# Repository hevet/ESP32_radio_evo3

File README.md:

# ESP32 Web Radio Evo3 (Evolution 3)

<p align="center">

</p>

## Overview
This is project of Internet Radio Streamer called "Evo". Hardware was buid using EPS32-S3 and DAC codec PCM5102A. Construction allows to listen varius music station from all around the world.
Working properly with streams coded in MP3, AAC, VORBIS and FLAC up to 2000kbit! Support all operations like volume control, stations changes, memory bank change, power on/off on single rotary 
encoder. Support infrared remote controls working on NEC standars (38kHz) and full control over web page and Android APP.

Many people is mixing wiht others (yoRadio) - Evo is NOT based on yoRadio. Evo Radio streamer was developed entirely in Poland.

Functions:
- Internet radio stream station from bank files (can be stored on SD card/internal LittleFS or downloaded from GitHub)
- I2S simple PCM5102A decoder support
- Full web server integrated for controling from desktop computer or mobile phone
- OLED Display SSD1322, SH1122 (256px x 64px)
- Single rotary encoder operations 
- OTA updates directlly from web page
- SD card /LittleFS content review/upload/download/delete by web page
- VUmeters add as some visualization on OLED
- 16 Banks with 99 station per each Bank support
- Polish fonts add for coorrect display station strings
- 3-point Equalizer
- ADC resistance keyboard support for easy inegration in FM converted tuners
- Power on/off from remote controller
- Sleep timer

## FLAC stations
<p>Smoothjazz.com.pl 16bit 1Mbps and AIDA Radio 24bit 2Mpbs!
<br>

<p>

## Display Modes

## Hardware
- ESP32-S3 dev. module with internal antena or external antena connector
- 256x64 OLED display based on SSD1322 or SH1122 driver IC
- 1x Rotary encoder
- IR 38KHz receiver (Vishay TSOP2238)
- PCB design stored in repository
- Housing avalivle as ready to print STL files
- SD or micro SD card reader (optional)
 
## Software
Project was coded in Arduino but ready main.cpp for Platformio files avalable and also tested

How to compile (Arduino):
- Install fresh Arduino (currently 2.3.6)
- After instalation add ESP32 board package by Espressif (this operation will take some time)
- Install bellow libs inside Arduino (library manager): 
  ESP32-audioI2S, 
  ezButton, 
  U8g2, 
  WiFiManager

Proper version of all libs are placed on top of source code ino file
For Platformio look into src folder -> Platformio folder and Platformio.ini file.

## Software Dependencies
[ESP Espressif 3.3.7 libs]

[3rd-party libs]
- ESP32-audioI2S-master 3.4.4
- U8g2 2.36.5
- ezButton 1.0.4
- WiFiManager 2.0.17
- ESP Async WebServer 3.10.0
- Async TCP 3.4.10

## Web server
Radio has buit in small web server with simple webpage for list stations, bank select, volume control and access to settings menu

## Radio Browser
The built-in Radio Browser search page allows you to search for various radio stations around the world, and play or test them instantly on Evo Radio.

## Android APK
There is small Android APK wirtten for this project giving possibily to direct control Evo radio from mobile phone.

There is a pre-coded remote controller RC-406 (Kenwood clone). You can change the settings via a simple web interface or by editing the remote.txt file stored in memory (SD card or internal flash).

Key mapping:

## Usage
Minimum radio can be build only with two compoents - ESP32-S3 dev. module and PCM5102A. In this configartion last station, memory bank number and volume will be stored in EEPROM. Control is possible via web page or IR remote control RC-406.
For full experience connect encoder, IR receiver.

NEC standard codes for remote controler are stored in "remote.txt" file. You can learn your IR remote by webpage. 

### Radio Station URLs
The radio streams URL addresses are defined in banks files, each bank is downloaded at first run and stored on SD card as separate txt file: Bank01.txt, Bank02.txt etc.
Each of banks can store 99 station. You can modify the station by changing the URLs in the code. Bank files are stored here:

STATIONS_URL1 "https://raw.githubusercontent.com/dzikakuna/ESP32_radio_streams/main/bank01.txt"
STATIONS_URL2 "https://raw.githubusercontent.com/dzikakuna/ESP32_radio_streams/main/bank02.txt"
STATIONS_URL3 "https://raw.githubusercontent.com/dzikakuna/ESP32_radio_streams/main/bank03.txt"
...
STATIONS_URL16 "https://raw.githubusercontent.com/dzikakuna/ESP32_radio_streams/main/bank16.txt"

## License
This project is open-source and licensed under the [MIT License](https://opensource.org/licenses/MIT). 
Feel free to contribute and improve the code.

MIT License
Copyright (c) 2025 [Grzegorz / Dzikakuna / Robgold ]

Permission is hereby granted, free of charge, to any person obtaining a copy of this software and associated documentation files (the "Software"), to deal in the Software without restriction, including without limitation the rights to use, copy, modify, merge, publish, distribute, sublicense, and/or sell copies of the Software, and to permit persons to whom the Software is furnished to do so, subject to the following conditions:
The above copyright notice and this permission notice shall be included in all copies or substantial portions of the Software.
THE SOFTWARE IS PROVIDED "AS IS", WITHOUT WARRANTY OF ANY KIND, EXPRESS OR IMPLIED, INCLUDING BUT NOT LIMITED TO THE WARRANTIES OF MERCHANTABILITY, FITNESS FOR A PARTICULAR PURPOSE AND NONINFRINGEMENT. IN NO EVENT SHALL THE AUTHORS OR COPYRIGHT HOLDERS BE LIABLE FOR ANY CLAIM, DAMAGES OR OTHER LIABILITY, WHETHER IN AN ACTION OF CONTRACT, TORT OR OTHERWISE, ARISING FROM, OUT OF OR IN CONNECTION WITH THE SOFTWARE OR THE USE OR OTHER DEALINGS IN THE SOFTWARE.

## Others
- This project was inspired by https://github.com/sarunia/ESP32_radio_player_v2
- More informations you can read here: https://www.elektroda.pl/rtvforum/topic4041603.html

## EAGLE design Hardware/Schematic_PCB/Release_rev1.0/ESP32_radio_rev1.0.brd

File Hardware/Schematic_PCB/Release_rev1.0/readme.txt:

ESP32 Internet Radio schematic & PCB file - rev 1.0
Gerbers attached. Drills in english (2.4) and metric format (3.3)
TootTable attached from CAM system.

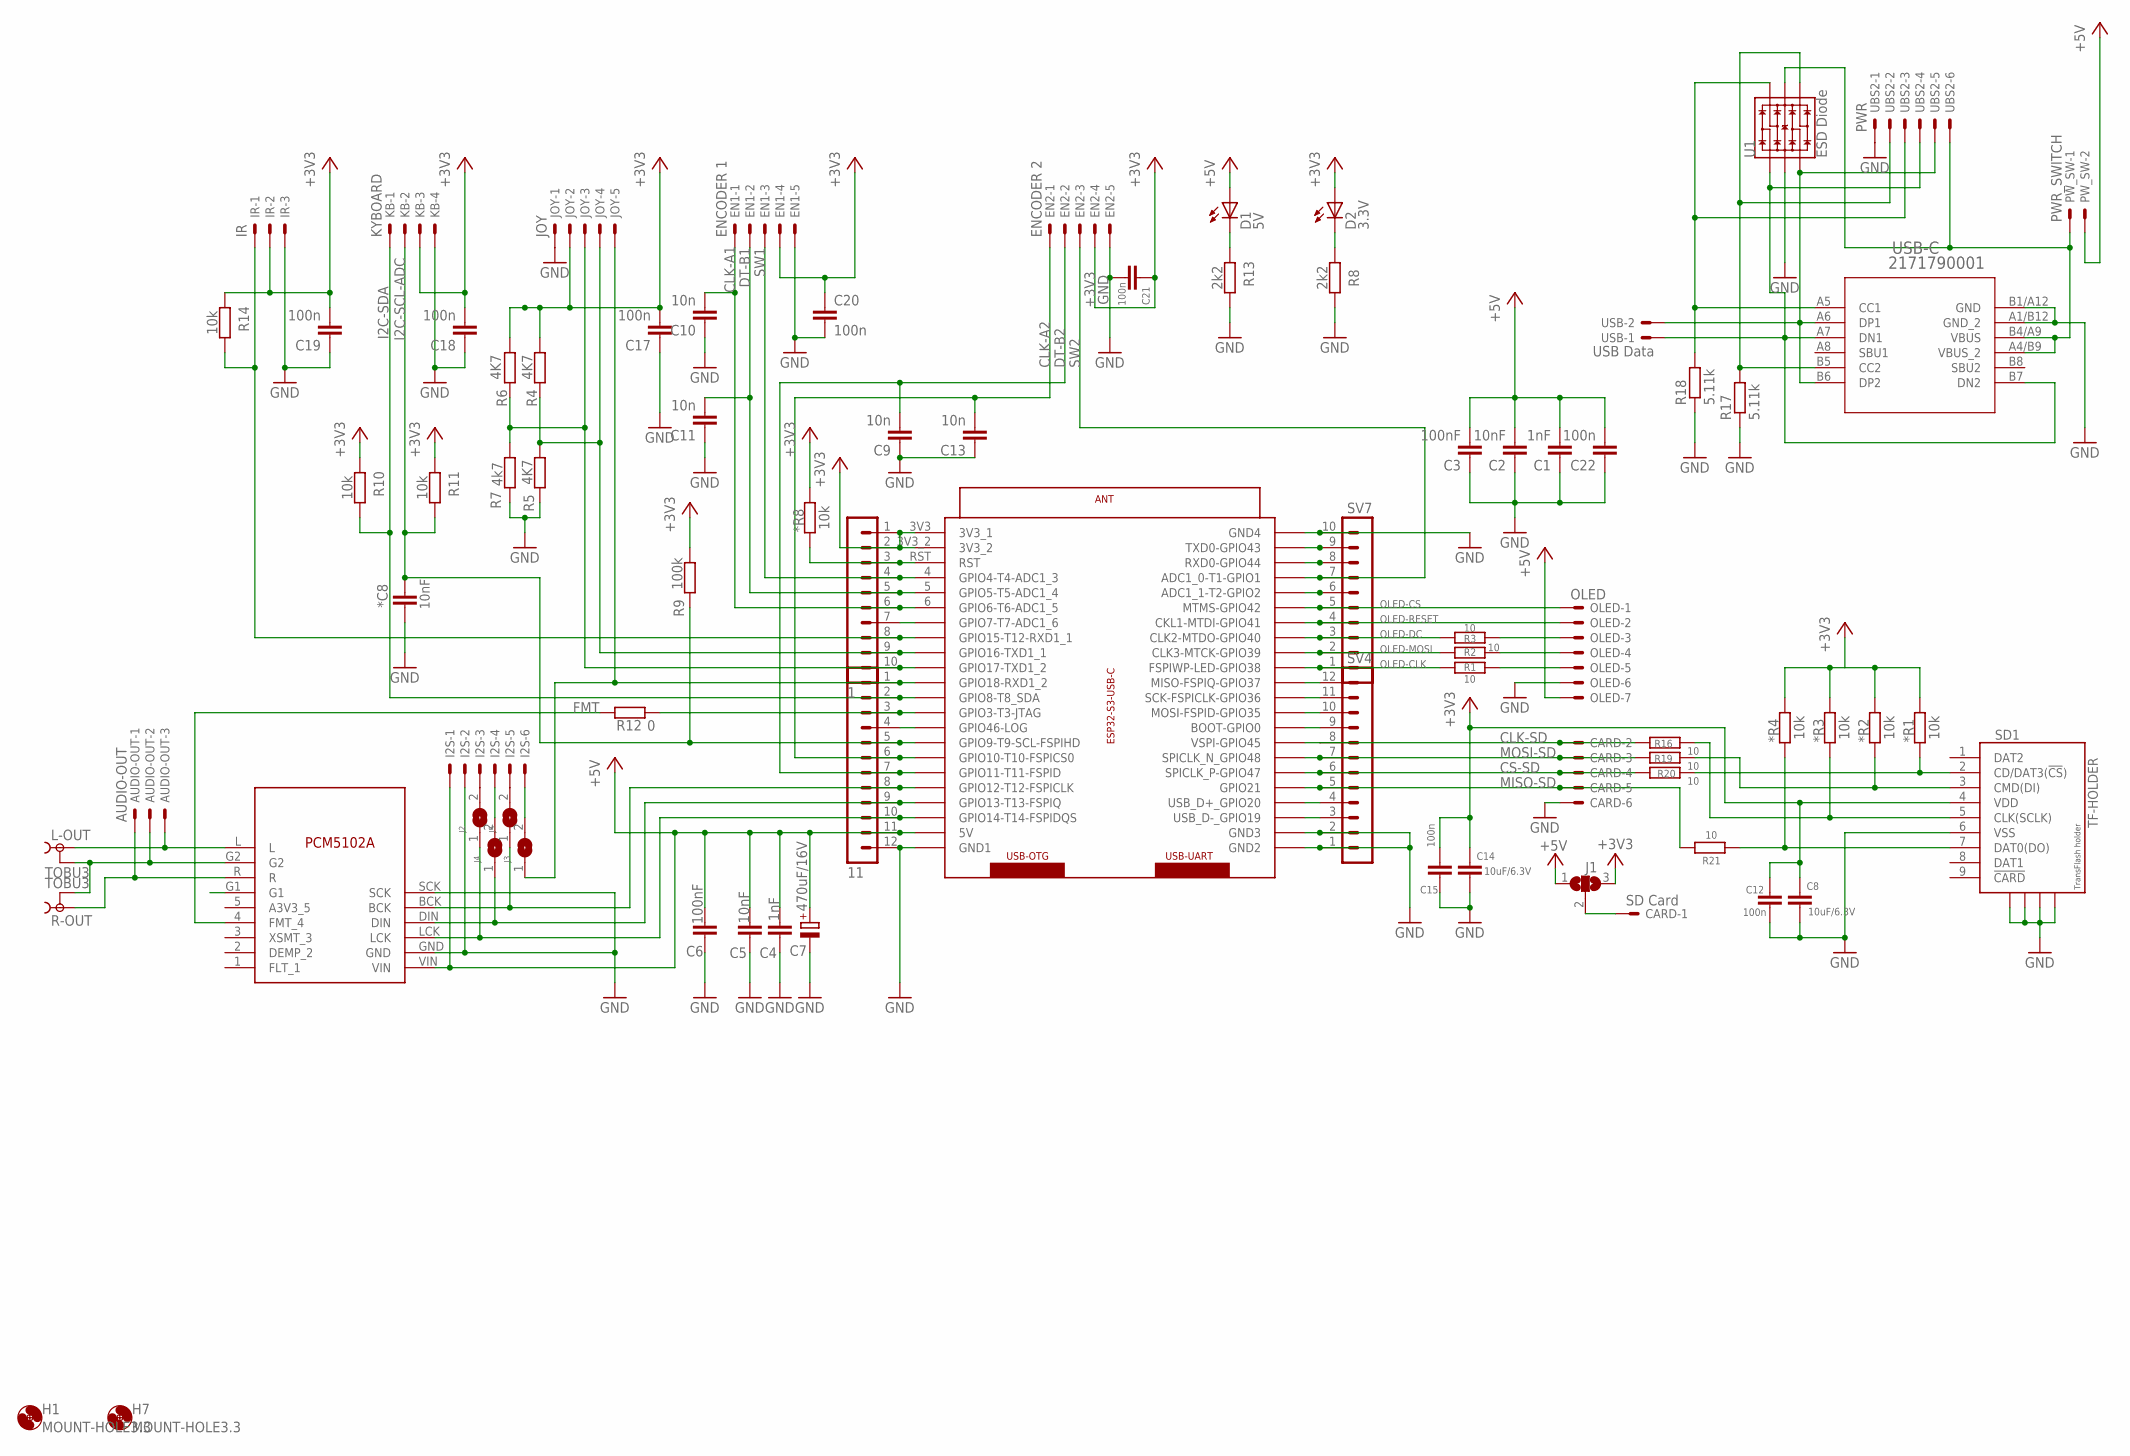
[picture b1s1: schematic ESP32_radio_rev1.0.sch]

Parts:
1: MA10-1
11: MA12-1
*C8: 10nF; C0603
*R1, *R2, *R3, *R4, *R8: 10k; R0603
AUDIO-OUT: AUDIO-OUT; JST-XH-03-PACKAGE-LONG-PAD
C1, C4: 1nF; C0603
C2, C5: 10nF; C0603
C3, C6: 100nF; C0603
C7: 470uF/16V; 150CLZ-1010
C8, C14: 10uF/6.3V; C1210
C9, C10, C11, C13: 10n; C0603
C12, C15, C17, C18, C19, C20, C21, C22: 100n; C0603
CARD: SD Card; JST-XH-06-PACKAGE-LONG-PAD
D1: 5V; CHIP-LED0805
D2: 3.3V; CHIP-LED0805
EN1: ENCODER 1; JST-XH-05-PACKAGE-LONG-PAD
EN2: ENCODER 2; JST-XH-05-PACKAGE-LONG-PAD
H1, H7: MOUNT-HOLE3.3; 3,3
I2S: JST-XH-06-PIN-LONG-PAD; JST-XH-06-PACKAGE-LONG-PAD
IR: IR; JST-XH-03-PACKAGE-LONG-PAD
J1: SJ2W; SJ_2
J2, J3, J4, J5: SJ
JOY: JOY; JST-XH-05-PACKAGE-LONG-PAD
KB: KYBOARD; JST-XH-04-PACKAGE-LONG-PAD
L-OUT: TOBU3
M2: I2S_PCM_51XX_SOUNDCARD; I2S_PCM_5100_SOUNDCARD
OLED: OLED; JST-XH-07-PACKAGE-LONG-PAD
PW_SW: PWR_SWITCH; JST-XH-02-PACKAGE-LONG-PAD
R1, R2, R3, R16, R19, R20, R21: 10; R0603
R4, R5, R6: 4K7; R0603
R7: 4k7; R0603
R8, R13: 2k2; R0603
R9: 100k; R0603
R10, R11, R14: 10k; R0603
R12: 0; R0603
R17, R18: 5.11k; R0603
R-OUT: TOBU3
SD1: TF-HOLDER; TF-PULL
SV4: MA12-1
SV7: MA10-1
U1: ESD Diode; SOT-23-6
U$1: ESP32-S3-USBC
UBS2: PWR; JST-XH-06-PACKAGE-LONG-PAD
USB: USB Data; JST-XH-02-PACKAGE-LONG-PAD
USB-C: 2171790001; 2171790001_MOL

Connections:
5V_USB: PW_SW.1, U1.5 (VCC), UBS2.6, USB-C.A4/B9 (VBUS_2), USB-C.B4/A9 (VBUS)
+3V3: 1.1, 1.2, *R1.1, *R2.1, *R3.1, *R4.1, *R8.1, C8.1, C12.2, C14.1, C15.2, C17.2, C18.2, C19.2, C20.1, C21.1, D2.A, EN1.4, EN2.4, IR.2, J1.3, JOY.2, KB.3, R4.2, R6.2, R9.2, R10.2, R11.2, R14.2, SD1.4 (VDD), U$1.3V3 (3V3_1), U$1.3V3_2
+5V: 11.11, C1.2, C2.2, C3.2, C4.2, C5.2, C6.2, C7.+, C22.2, D1.A, I2S.1, J1.1, M2.VIN, OLED.7, PW_SW.2, U$1.5V
ANALOGGND: AUDIO-OUT.2, L-OUT.2, L-OUT.2@1 (2), L-OUT.2@2 (2), M2.G2, R-OUT.2, R-OUT.2@1 (2), R-OUT.2@2 (2)
CLK-A1: 1.6, C10.2, EN1.1, U$1.6 (GPIO6-T6-ADC1_5)
CLK-A2: 11.6, C13.2, EN2.1, U$1.10 (GPIO10-T10-FSPICS0)
CLK-SD: CARD.2, R16.1, SV4.8, U$1.45 (VSPI-GPIO45)
CS-SD: CARD.4, R20.1, SV4.6, U$1.47 (SPICLK_P-GPIO47)
DN: U1.1 (IO1), UBS2.4, USB.1, USB-C.A7 (DN1), USB-C.B7 (DN2)
DP: U1.3 (IO2), UBS2.5, USB.2, USB-C.A6 (DP1), USB-C.B6 (DP2)
DT-B1: 1.5, C11.2, EN1.2, U$1.5 (GPIO5-T5-ADC1_4)
DT-B2: 11.7, C9.2, EN2.2, U$1.11 (GPIO11-T11-FSPID)
FMT: M2.4 (FMT_4), R12.2
FMT1: 11.4, U$1.46 (GPIO46-LOG)
GND: 11.12, *C8.2, C1.1, C2.1, C3.1, C4.1, C5.1, C6.1, C7.-, C8.2, C9.1, C10.1, C11.1, C12.1, C13.1, C14.2, C15.1, C17.1, C18.1, C19.1, C20.2, C21.2, C22.1, CARD.6, EN1.5, EN2.5, I2S.2, IR.3, JOY.1, KB.4, M2.GND, M2.SCK, OLED.6, R5.1, R7.1, R8.1, R13.1, R17.1, R18.1, SD1.6 (VSS), SD1.S1, SD1.S2, SD1.S3, SD1.S4, SV4.1, SV4.2, SV7.10, U1.2 (VSS), U$1.GND1, U$1.GND2, U$1.GND3, U$1.GND4, UBS2.1, USB-C.A1/B12 (GND_2), USB-C.B1/A12 (GND)
I2C-SCL-ADC: 11.5, *C8.1, KB.2, R9.1, R11.1, U$1.9 (GPIO9-T9-SCL-FSPIHD)
I2C-SDA: 11.2, KB.1, R10.1, U$1.8 (GPIO8-T8_SDA)
MISO-SD: CARD.5, R21.1, SV4.5, U$1.21 (GPIO21)
MOSI-SD: CARD.3, R19.1, SV4.7, U$1.48 (SPICLK_N_GPIO48)
unnamed: AUDIO-OUT.1, M2.R, R-OUT.1
unnamed: AUDIO-OUT.3, L-OUT.1, M2.L
unnamed: OLED.5, R1.2
unnamed: OLED.4, R2.2
unnamed: OLED.3, R3.2
unnamed: *R4.2, R21.2, SD1.7 (DAT0(DO))
unnamed: 1.10, JOY.3, R6.1, R7.2, U$1.17 (GPIO17-TXD1_2)
unnamed: 11.1, J3.1, JOY.5, U$1.18 (GPIO18-RXD1_2)
unnamed: 11.10, J2.1, M2.LCK, U$1.14 (GPIO14-T14-FSPIDQS)
unnamed: 1.3, *R8.2, U$1.RST
unnamed: *R1.2, R20.2, SD1.2 (CD/DAT3(!CS!))
unnamed: 1.9, JOY.4, R4.1, R5.2, U$1.16 (GPIO16-TXD1_1)
unnamed: 11.9, J4.1, M2.DIN, U$1.13 (GPIO13-T13-FSPIQ)
unnamed: 11.8, J5.1, M2.BCK, U$1.12 (GPIO12-T12-FSPICLK)
unnamed: 1.7, U$1.7 (GPIO7-T7-ADC1_6)
unnamed: SV7.6, U$1.2 (ADC1_1-T2-GPIO2)
unnamed: 1.8, IR.1, R14.1, U$1.15 (GPIO15-T12-RXD1_1)
unnamed: D2.C, R8.2
unnamed: SV7.8, U$1.44 (RXD0-GPIO44)
unnamed: SV7.9, U$1.43 (TXD0-GPIO43)
unnamed: SV4.3, U$1.19 (USB_D-_GPIO19)
unnamed: SV4.4, U$1.20 (USB_D+_GPIO20)
unnamed: SV4.9, U$1.0 (BOOT-GPIO0)
unnamed: SV4.10, U$1.35 (MOSI-FSPID-GPIO35)
unnamed: SV4.11, U$1.36 (SCK-FSPICLK-GPIO36)
unnamed: SV4.12, U$1.37 (MISO-FSPIQ-GPIO37)
unnamed: 11.3, R12.1, U$1.3 (GPIO3-T3-JTAG)
unnamed: D1.C, R13.2
unnamed: CARD.1, J1.2
unnamed: *R2.2, R19.2, SD1.3 (CMD(DI))
unnamed: *R3.2, R16.2, SD1.5 (CLK(SCLK))
unnamed: I2S.3, J2.2
unnamed: R17.2, U1.4 (IO3), UBS2.2, USB-C.B5 (CC2)
unnamed: R18.2, U1.6 (IO4), UBS2.3, USB-C.A5 (CC1)
unnamed: I2S.6, J3.2
unnamed: I2S.5, J5.2
unnamed: I2S.4, J4.2
OLED-CLK: R1.1, SV7.1, U$1.38 (FSPIWP-LED-GPIO38)
OLED-CS: OLED.1, SV7.5, U$1.42 (MTMS-GPIO42)
OLED-DC: R3.1, SV7.3, U$1.40 (CLK2-MTDO-GPIO40)
OLED-MOSI: R2.1, SV7.2, U$1.39 (CLK3-MTCK-GPIO39)
OLED-RESET: OLED.2, SV7.4, U$1.41 (CKL1-MTDI-GPIO41)
SW1: 1.4, EN1.3, U$1.4 (GPIO4-T4-ADC1_3)
SW2: EN2.3, SV7.7, U$1.1 (ADC1_0-T1-GPIO1)

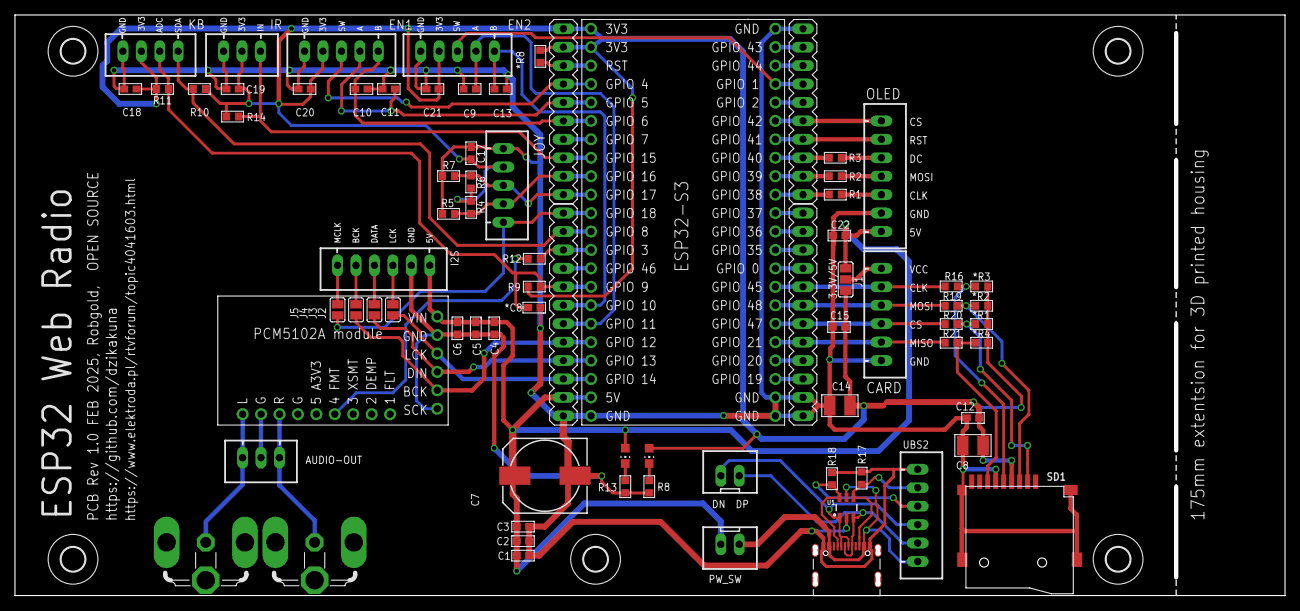
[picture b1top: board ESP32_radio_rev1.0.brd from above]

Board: 2 copper layers, 175.0 x 80.0 mm, 82 parts (0 on the bottom side), 63 nets.

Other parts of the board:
H2, H3, H8: MOUNT-HOLE3.3; 3,3

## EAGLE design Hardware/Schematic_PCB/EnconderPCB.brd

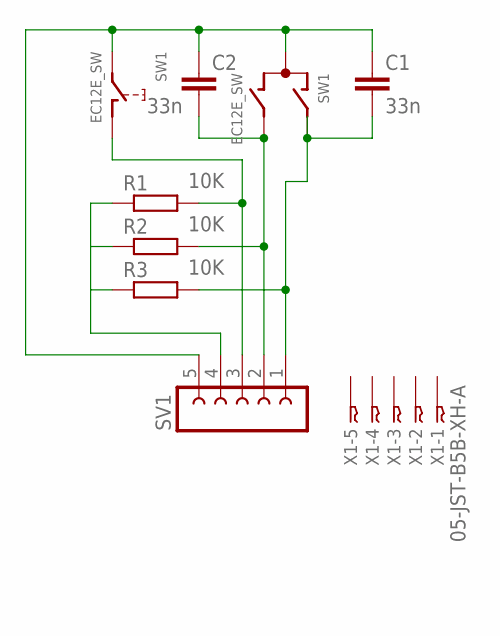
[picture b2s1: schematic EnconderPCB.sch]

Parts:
C1, C2: 33n; C0603
R1, R2, R3: 10K; R0603
SV1: FE05-1
SW1: EC12E_SW; ALPS_EC12E_SW
X1: 05-JST-B5B-XH-A; B5B-XH

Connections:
unnamed: C1.2, R3.2, SV1.1, SW1.A
unnamed: C2.2, R2.2, SV1.2, SW1.B
unnamed: R1.2, SV1.3, SW1.D (1)
unnamed: C1.1, C2.1, SV1.5, SW1.C, SW1.E (2)
unnamed: R1.1, R2.1, R3.1, SV1.4

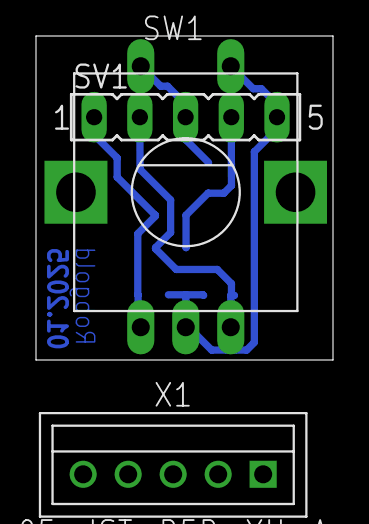
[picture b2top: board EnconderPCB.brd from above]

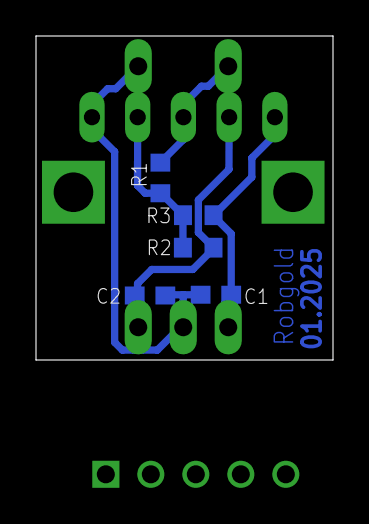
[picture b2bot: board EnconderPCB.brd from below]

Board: 2 copper layers, 16.5 x 18.0 mm, 8 parts (5 on the bottom side), 5 nets.

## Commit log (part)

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2025-01-10 ESP32_radio_evo3
2025-01-10 ESP32 Radio evo3.1
2025-01-11 Case/Housing STL files update
2025-01-12 Update - fonts, stl files for 3d print
2025-01-12 Update pl fonts
2025-01-12 Update
    Bank URLs updated to own GitHub,
    Option for update from server alredy downloaded Bank files add
2025-01-16 Update
    Moved stations list to PSRAM,
    Add simple Web server
2025-01-19 Tests - experimental
2025-02-27 TCP lib update for FLAC stations
2025-03-01 PCB Gerbers for review
2025-03-02 Schematic & PCB update
2025-03-09 Evo3.16 release
    Revision capable to work without SD Card
2025-03-15 Housing backplate update
2025-03-18 Update Arduino and Platformio
2025-03-20 Update src + add icon for browser
2025-03-23 Update
    Global variable controling length of station name add.
2025-04-08 Update 3.17.53
    Corrected Bank change over web page, station change by enocder.
2025-04-11 Cleaning
2025-04-15 RemoteControlMap_rev1.00
2025-04-19 Update 3.17.65
    New one menu button, new bank editor v1.05.
2025-05-10 Update 3.17.77
    Web page new layout, WebSockets add
2025-06-07 Update 3.18.04
    New Scroller Formater, 1250 to UTF8 in Station String formater add.
2025-06-07 Update Evo3.18.05
    Correction in win1250toUtf8 function.
2025-06-08 Update Evo3.18.06
    New VUmeter with 1px increase, Peak&Hold function added
2025-07-16 3.18.13 update
2026-05-09 Update 3.20.14
    ESP32 Core: 3.3.8 + "FLAC" lwip libs recompiled based on IDF 5.5.4, Arduino: 2.3.6

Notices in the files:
parts and their libraries:
USB-C_2: COPYRIGHT: Copyright (C) 2025 GRo
SparkFun-DiscreteSemi: Licensing: Creative Commons ShareAlike 4.0 International - https://creativecommons.org/licenses/by-sa/4.0
